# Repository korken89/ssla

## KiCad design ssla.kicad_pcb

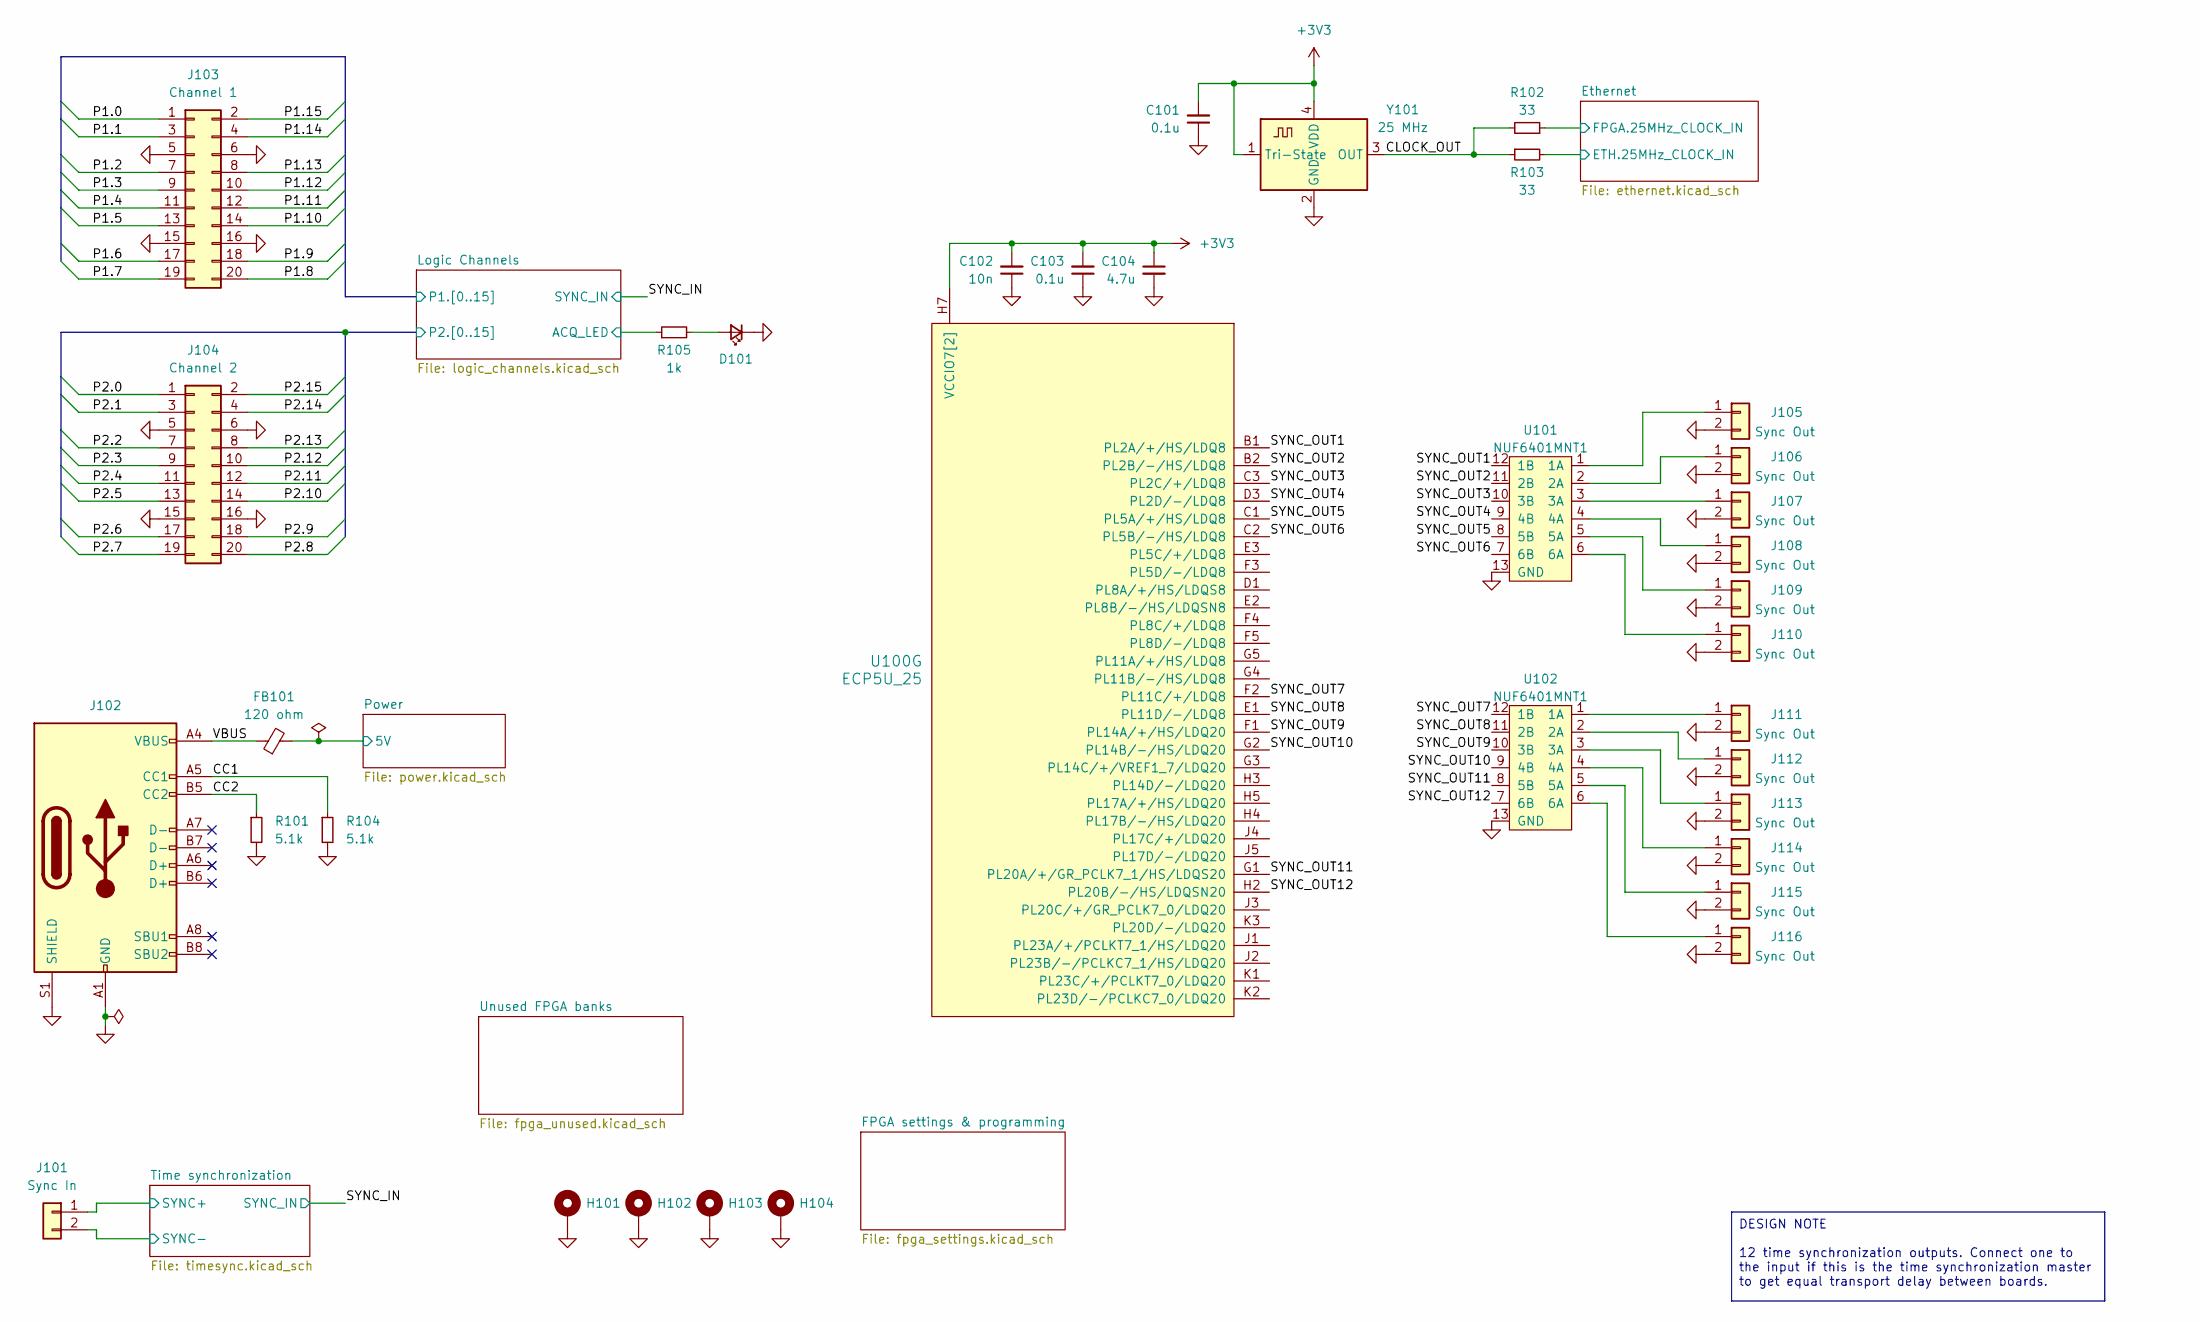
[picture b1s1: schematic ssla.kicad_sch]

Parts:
C101, C103: 0.1u; C_0402_1005Metric; LCSC C307331
C102: 10n; C_0402_1005Metric; LCSC C15195
C104: 4.7u; C_0402_1005Metric; LCSC C23733
D101: RED; LED_0603_1608Metric
FB101: 120 ohm; L_0402_1005Metric; LCSC C88970
H101, H102, H103, H104: MountingHole_Pad; MountingHole_2.2mm_M2_Pad_Via
J101: Sync In; JST_PH_B2B-PH-K_1x02_P2.00mm_Vertical; LCSC C158012
J102: USB_C_Receptacle_USB2.0_14P; USB_C_Receptacle_GCT_USB4105-xx-A_16P_TopMnt_Horizontal; LCSC C165948
J103: Channel 1; IDC-Header_2x10_P2.54mm_Vertical; LCSC C221051
J104: Channel 2; IDC-Header_2x10_P2.54mm_Vertical; LCSC C221051
J105, J106, J107, J108, J109, J110, J111, J112, J113, J114, J115, J116: Sync Out; JST_PH_B2B-PH-K_1x02_P2.00mm_Vertical; LCSC C158012
R101, R104: 5.1k; R_0402_1005Metric; LCSC C25905
R102, R103: 33; R_0402_1005Metric; LCSC C25105
R105: 1k; R_0402_1005Metric; LCSC C11702
U100: ECP5U_25; BGA-256_14.0x14.0mm_Layout16x16_P0.8mm_Ball0.45mm_Pad0.32mm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
U101, U102: NUF6401MNT1; DFN-12-1EP_1.35x3mm_P0.5mm; LCSC C233491
Y101: 25 MHz; Oscillator_SMD_SiT_PQFN-4Pin_2.0x1.6mm; LCSC C669080

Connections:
+3V3: C101.2, C102.2, C103.2, C104.1, U100.H6 (VCCIO7[2]), U100.H7 (VCCIO7[2]), Y101.1 (Tri-State), Y101.4 (VDD); also elsewhere on the board
/CC1: J102.A5 (CC1), R104.1
/CC2: J102.B5 (CC2), R101.1
/CLOCK_OUT: R102.2, R103.1, Y101.3 (OUT)
/Ethernet/ETH.25MHz_CLOCK_IN: R103.2; also elsewhere on the board
/Ethernet/FPGA.25MHz_CLOCK_IN: R102.1; also elsewhere on the board
/Logic Channels/ACQ_LED: R105.1; also elsewhere on the board
/Logic Channels/P1.0: J103.1; also elsewhere on the board
/Logic Channels/P1.1: J103.3; also elsewhere on the board
/Logic Channels/P1.2: J103.7; also elsewhere on the board
/Logic Channels/P1.3: J103.9; also elsewhere on the board
/Logic Channels/P1.4: J103.11; also elsewhere on the board
/Logic Channels/P1.5: J103.13; also elsewhere on the board
/Logic Channels/P1.6: J103.17; also elsewhere on the board
/Logic Channels/P1.7: J103.19; also elsewhere on the board
/Logic Channels/P1.8: J103.20; also elsewhere on the board
/Logic Channels/P1.9: J103.18; also elsewhere on the board
/Logic Channels/P1.10: J103.14; also elsewhere on the board
/Logic Channels/P1.11: J103.12; also elsewhere on the board
/Logic Channels/P1.12: J103.10; also elsewhere on the board
/Logic Channels/P1.13: J103.8; also elsewhere on the board
/Logic Channels/P1.14: J103.4; also elsewhere on the board
/Logic Channels/P1.15: J103.2; also elsewhere on the board
/Logic Channels/P2.0: J104.1; also elsewhere on the board
/Logic Channels/P2.1: J104.3; also elsewhere on the board
/Logic Channels/P2.2: J104.7; also elsewhere on the board
/Logic Channels/P2.3: J104.9; also elsewhere on the board
/Logic Channels/P2.4: J104.11; also elsewhere on the board
/Logic Channels/P2.5: J104.13; also elsewhere on the board
/Logic Channels/P2.6: J104.17; also elsewhere on the board
/Logic Channels/P2.7: J104.19; also elsewhere on the board
/Logic Channels/P2.8: J104.20; also elsewhere on the board
/Logic Channels/P2.9: J104.18; also elsewhere on the board
/Logic Channels/P2.10: J104.14; also elsewhere on the board
/Logic Channels/P2.11: J104.12; also elsewhere on the board
/Logic Channels/P2.12: J104.10; also elsewhere on the board
/Logic Channels/P2.13: J104.8; also elsewhere on the board
/Logic Channels/P2.14: J104.4; also elsewhere on the board
/Logic Channels/P2.15: J104.2; also elsewhere on the board
/Power/5V: FB101.2; also elsewhere on the board
/SYNC_OUT1: U100.B1 (PL2A/+/HS/LDQ8), U101.12 (1B)
/SYNC_OUT2: U100.B2 (PL2B/-/HS/LDQ8), U101.11 (2B)
/SYNC_OUT3: U100.C3 (PL2C/+/LDQ8), U101.10 (3B)
/SYNC_OUT4: U100.D3 (PL2D/-/LDQ8), U101.9 (4B)
/SYNC_OUT5: U100.C1 (PL5A/+/HS/LDQ8), U101.8 (5B)
/SYNC_OUT6: U100.C2 (PL5B/-/HS/LDQ8), U101.7 (6B)
/SYNC_OUT7: U100.F2 (PL11C/+/LDQ8), U102.12 (1B)
/SYNC_OUT8: U100.E1 (PL11D/-/LDQ8), U102.11 (2B)
/SYNC_OUT9: U100.F1 (PL14A/+/HS/LDQ20), U102.10 (3B)
/SYNC_OUT10: U100.G2 (PL14B/-/HS/LDQ20), U102.9 (4B)
/SYNC_OUT11: U100.G1 (PL20A/+/GR_PCLK7_1/HS/LDQS20), U102.8 (5B)
/SYNC_OUT12: U100.H2 (PL20B/-/HS/LDQSN20), U102.7 (6B)
/Time synchronization/SYNC+: J101.1; also elsewhere on the board
/Time synchronization/SYNC-: J101.2; also elsewhere on the board
/VBUS: FB101.1, J102.A4 (VBUS), J102.A9 (VBUS), J102.B4 (VBUS), J102.B9 (VBUS)
GND: C101.1, C102.1, C103.1, C104.2, D101.1 (K), H101.1, H102.1, H103.1, H104.1, J102.A1 (GND), J102.A12 (GND), J102.B1 (GND), J102.B12 (GND), J102.S1 (SHIELD), J103.5, J103.6, J103.15, J103.16, J104.5, J104.6, J104.15, J104.16, J105.2, J106.2, J107.2, J108.2, J109.2, J110.2, J111.2, J112.2, J113.2, J114.2, J115.2, J116.2, R101.2, R104.2, U101.13 (GND), U102.13 (GND), Y101.2 (GND); also elsewhere on the board
unnamed: D101.2 (A), R105.2
unnamed: J105.1, U101.1 (1A)
unnamed: J106.1, U101.2 (2A)
unnamed: J107.1, U101.3 (3A)
unnamed: J108.1, U101.4 (4A)
unnamed: J109.1, U101.5 (5A)
unnamed: J110.1, U101.6 (6A)
unnamed: J111.1, U102.1 (1A)
unnamed: J112.1, U102.2 (2A)
unnamed: J113.1, U102.3 (3A)
unnamed: J114.1, U102.4 (4A)
unnamed: J115.1, U102.5 (5A)
unnamed: J116.1, U102.6 (6A)

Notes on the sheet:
DESIGN NOTE 12 time synchronization outputs. Connect one to the input if this is the time synchronization master to get equal transport delay between boards.

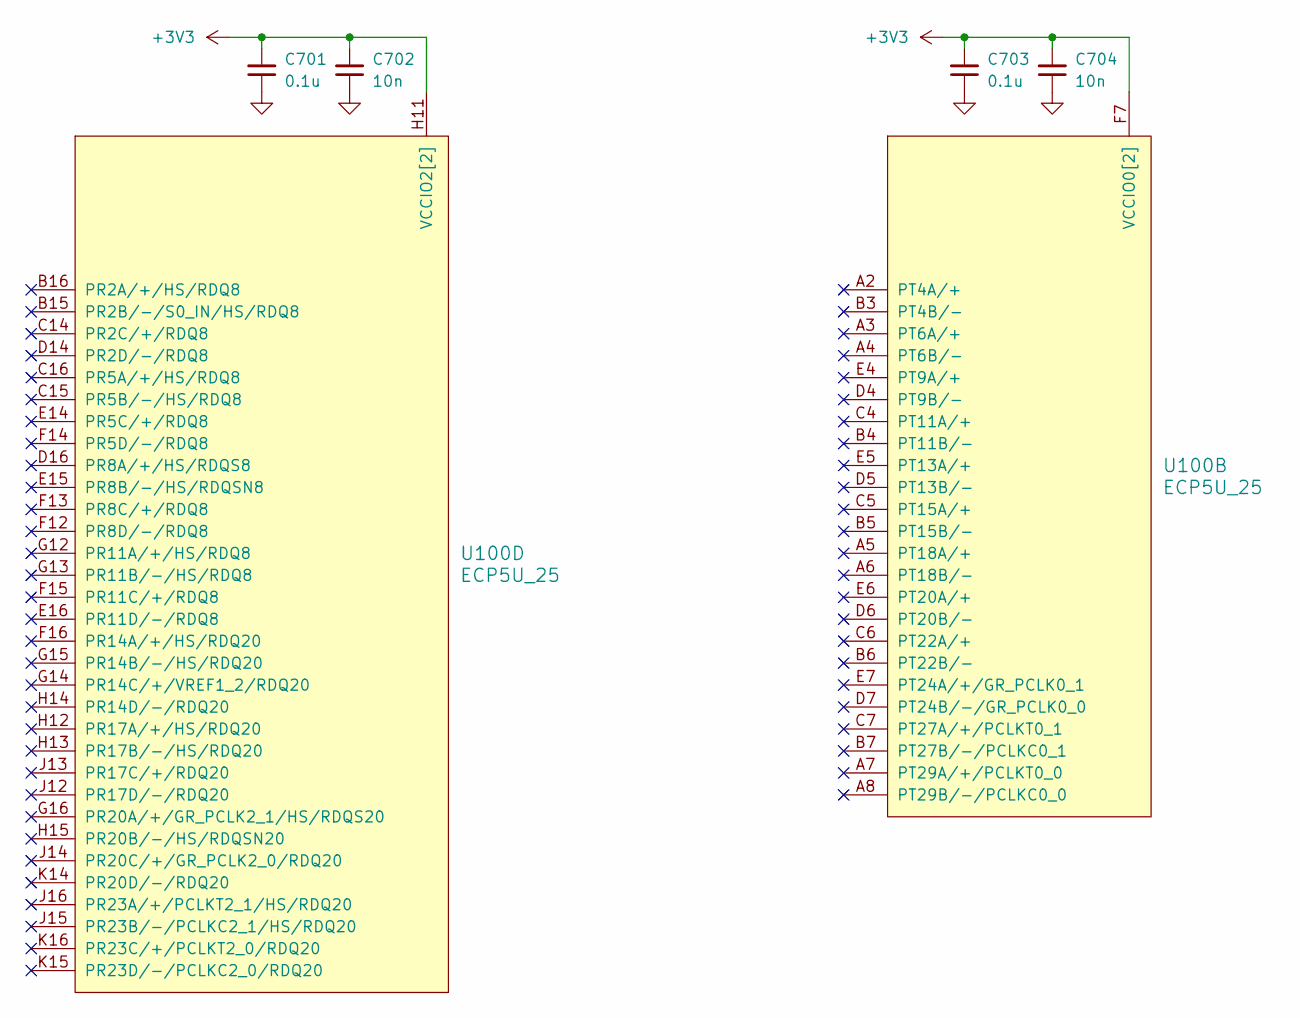
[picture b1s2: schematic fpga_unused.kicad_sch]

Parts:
C701, C703: 0.1u; C_0402_1005Metric; LCSC C307331
C702, C704: 10n; C_0402_1005Metric; LCSC C15195
U100: ECP5U_25; BGA-256_14.0x14.0mm_Layout16x16_P0.8mm_Ball0.45mm_Pad0.32mm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

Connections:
+3V3: C701.2, C702.2, C703.2, C704.2, U100.F6 (VCCIO0[2]), U100.F7 (VCCIO0[2]), U100.H11 (VCCIO2[2]), U100.J11 (VCCIO2[2]); also elsewhere on the board
GND: C701.1, C702.1, C703.1, C704.1; also elsewhere on the board

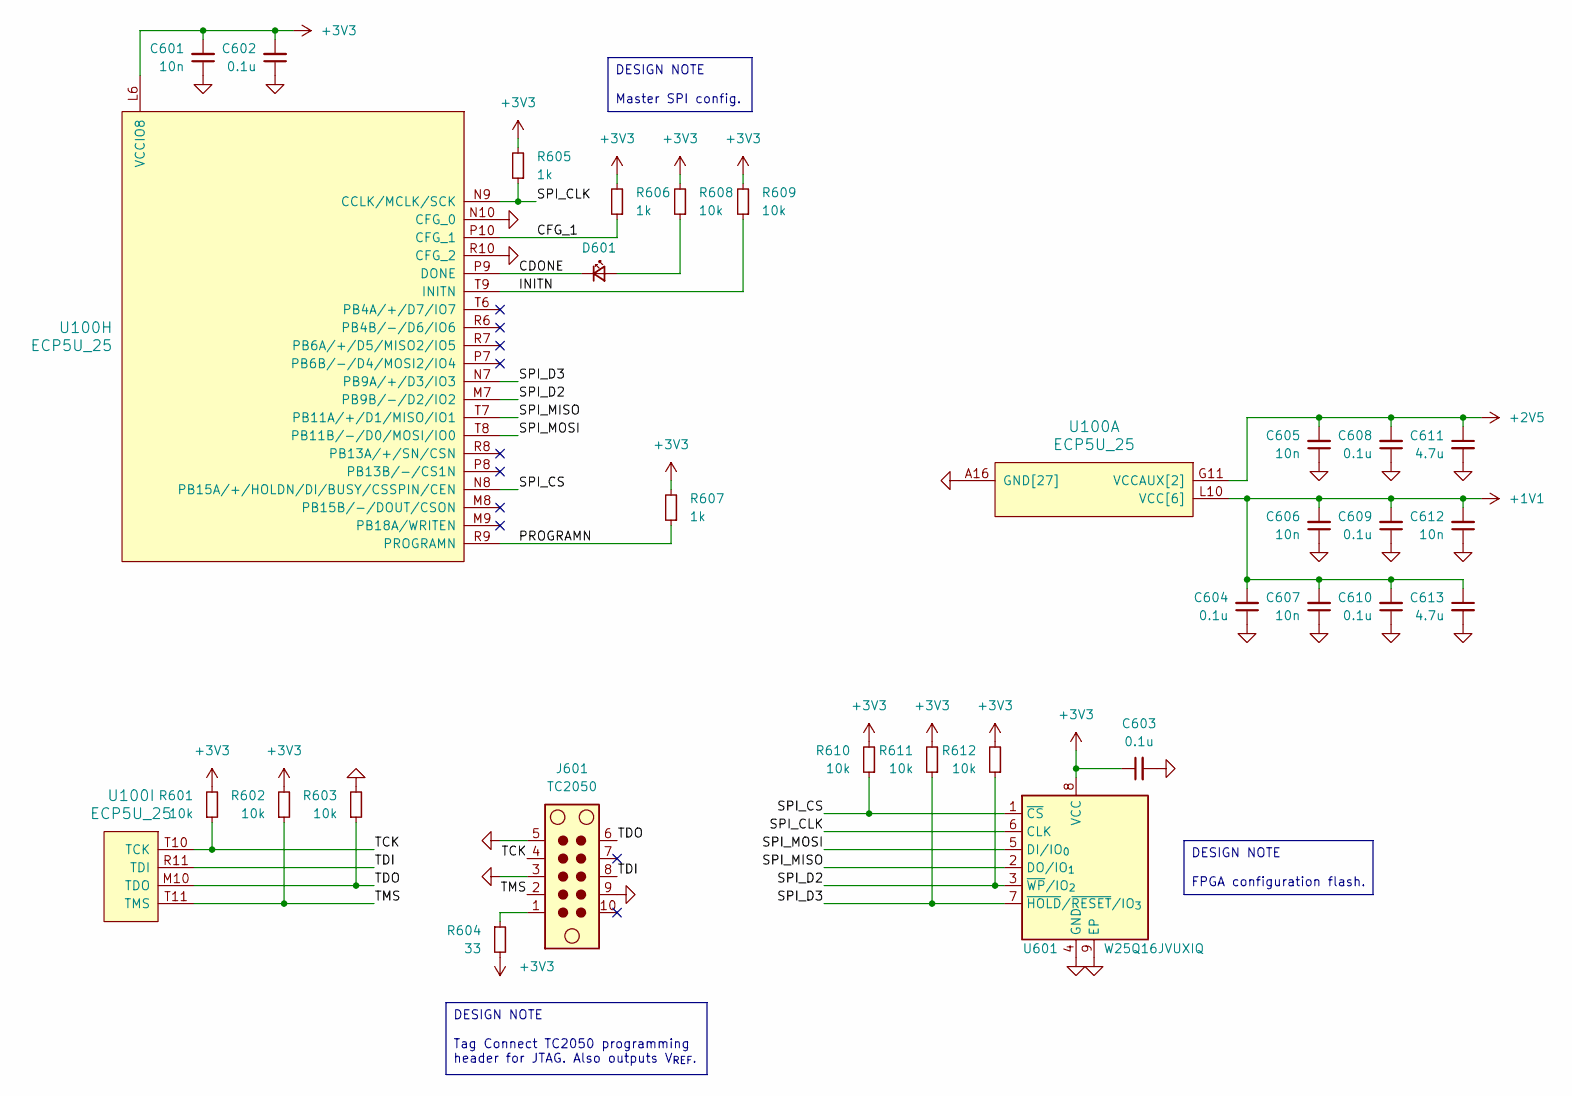
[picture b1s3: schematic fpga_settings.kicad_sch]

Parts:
C601, C605, C606, C607, C612: 10n; C_0402_1005Metric; LCSC C15195
C602, C603, C604, C608, C609, C610: 0.1u; C_0402_1005Metric; LCSC C307331
C611, C613: 4.7u; C_0402_1005Metric; LCSC C23733
D601: RED; LED_0603_1608Metric
J601: TC2050; Tag-Connect_TC2050-IDC-NL_2x05_P1.27mm_Vertical
R601, R602, R603, R608, R609, R610, R611, R612: 10k; R_0402_1005Metric; LCSC C25744
R604: 33; R_0402_1005Metric; LCSC C25105
R605, R606, R607: 1k; R_0402_1005Metric; LCSC C11702
U100: ECP5U_25; BGA-256_14.0x14.0mm_Layout16x16_P0.8mm_Ball0.45mm_Pad0.32mm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
U601: W25Q16JVUXIQ; Winbond_USON-8-1EP_3x2mm_P0.5mm_EP0.2x1.6mm; LCSC C2843335

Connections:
+1V1: C604.2, C606.2, C607.2, C609.2, C610.2, C612.2, C613.1, U100.G6 (VCC[6]), U100.G7 (VCC[6]), U100.G9 (VCC[6]), U100.L8 (VCC[6]), U100.L9 (VCC[6]), U100.L10 (VCC[6]); also elsewhere on the board
+2V5: C605.2, C608.2, C611.1, U100.G11 (VCCAUX[2]), U100.L7 (VCCAUX[2]); also elsewhere on the board
+3V3: C601.2, C602.2, C603.1, R601.2, R602.2, R604.2, R605.2, R606.2, R607.2, R608.2, R609.2, R610.2, R611.2, R612.2, U100.L6 (VCCIO8), U601.8 (VCC); also elsewhere on the board
/FPGA settings & programming/CDONE: D601.1 (K), U100.P9 (DONE)
/FPGA settings & programming/CFG_1: R606.1, U100.P10 (CFG_1)
/FPGA settings & programming/INITN: R609.1, U100.T9 (INITN)
/FPGA settings & programming/PROGRAMN: R607.1, U100.R9 (PROGRAMN)
/FPGA settings & programming/SPI_CLK: R605.1, U100.N9 (CCLK/MCLK/SCK), U601.6 (CLK)
/FPGA settings & programming/SPI_CS: R610.1, U100.N8 (PB15A/+/HOLDN/DI/BUSY/CSSPIN/CEN), U601.1 (~CS)
/FPGA settings & programming/SPI_D2: R612.1, U100.M7 (PB9B/-/D2/IO2), U601.3 (~WP/IO_{2})
/FPGA settings & programming/SPI_D3: R611.1, U100.N7 (PB9A/+/D3/IO3), U601.7 (~HOLD/~RESET/IO_{3})
/FPGA settings & programming/SPI_MISO: U100.T7 (PB11A/+/D1/MISO/IO1), U601.2 (DO/IO_{1})
/FPGA settings & programming/SPI_MOSI: U100.T8 (PB11B/-/D0/MOSI/IO0), U601.5 (DI/IO_{0})
/FPGA settings & programming/TCK: J601.4, R601.1, U100.T10 (TCK)
/FPGA settings & programming/TDI: J601.8, U100.R11 (TDI)
/FPGA settings & programming/TDO: J601.6, R603.1, U100.M10 (TDO)
/FPGA settings & programming/TMS: J601.2, R602.1, U100.T11 (TMS)
GND: C601.1, C602.1, C603.2, C604.1, C605.1, C606.1, C607.1, C608.1, C609.1, C610.1, C611.2, C612.1, C613.2, J601.3, J601.5, J601.9, R603.2, U100.A1 (GND[27]), U100.A16 (GND[27]), U100.D2 (GND[27]), U100.D15 (GND[27]), U100.F8 (GND[27]), U100.F9 (GND[27]), U100.G8 (GND[27]), U100.G10 (GND[27]), U100.H1 (GND[27]), U100.H8 (GND[27]), U100.H9 (GND[27]), U100.H10 (GND[27]), U100.H16 (GND[27]), U100.J8 (GND[27]), U100.J9 (GND[27]), U100.J10 (GND[27]), U100.K6 (GND[27]), U100.K7 (GND[27]), U100.K8 (GND[27]), U100.K9 (GND[27]), U100.K10 (GND[27]), U100.N2 (GND[27]), U100.N10 (CFG_0), U100.N15 (GND[27]), U100.R10 (CFG_2), U100.T1 (GND[27]), U100.T5 (GND[27]), U100.T12 (GND[27]), U100.T16 (GND[27]), U601.4 (GND), U601.9 (EP); also elsewhere on the board
unnamed: D601.2 (A), R608.1
unnamed: J601.1, R604.1

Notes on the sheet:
DESIGN NOTE FPGA configuration flash.
DESIGN NOTE Tag Connect TC2050 programming header for JTAG. Also outputs V_{REF}.
DESIGN NOTE Master SPI config.

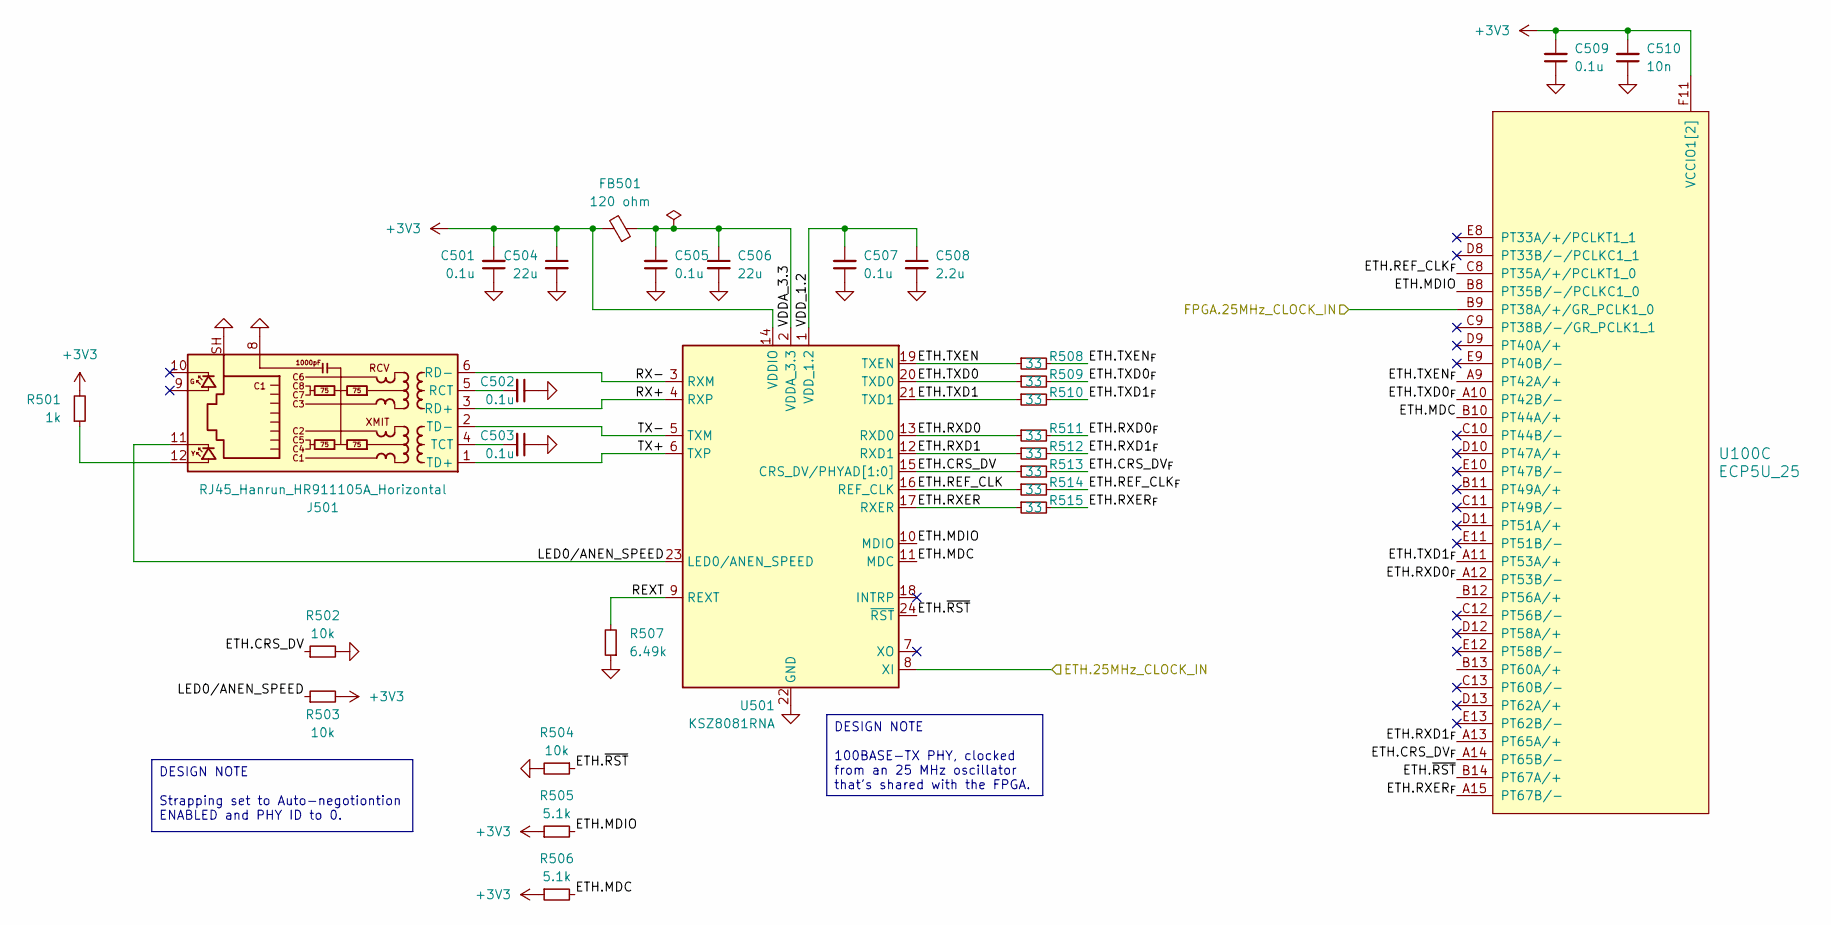
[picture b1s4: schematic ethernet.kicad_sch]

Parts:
C501, C502, C503, C505, C507, C509: 0.1u; C_0402_1005Metric; LCSC C307331
C504, C506: 22u; C_0603_1608Metric; LCSC C84419
C508: 2.2u; C_0402_1005Metric; LCSC C77002
C510: 10n; C_0402_1005Metric; LCSC C15195
FB501: 120 ohm; L_0402_1005Metric; LCSC C88970
J501: RJ45_Hanrun_HR911105A_Horizontal; LCSC C12074
R501: 1k; R_0402_1005Metric; LCSC C11702
R502, R503, R504: 10k; R_0402_1005Metric; LCSC C25744
R505, R506: 5.1k; R_0402_1005Metric; LCSC C25905
R507: 6.49k; R_0402_1005Metric; LCSC C25916
R508, R509, R510, R511, R512, R513, R514, R515: 33; R_0402_1005Metric; LCSC C25105
U100: ECP5U_25; BGA-256_14.0x14.0mm_Layout16x16_P0.8mm_Ball0.45mm_Pad0.32mm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
U501: KSZ8081RNA; QFN-24-1EP_4x4mm_P0.5mm_EP2.6x2.6mm; LCSC C100017

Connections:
+3V3: C501.2, C504.1, C509.2, C510.2, FB501.2, R501.2, R503.2, R505.1, R506.1, U100.F10 (VCCIO1[2]), U100.F11 (VCCIO1[2]), U501.14 (VDDIO); also elsewhere on the board
/Ethernet/ETH.25MHz_CLOCK_IN: U501.8 (XI); also elsewhere on the board
/Ethernet/ETH.CRS_DV: R502.1, R513.1, U501.15 (CRS_DV/PHYAD[1:0])
/Ethernet/ETH.CRS_DV_{F}: R513.2, U100.A14 (PT65B/-)
/Ethernet/ETH.MDC: R506.2, U100.B10 (PT44A/+), U501.11 (MDC)
/Ethernet/ETH.MDIO: R505.2, U100.B8 (PT35B/-/PCLKC1_0), U501.10 (MDIO)
/Ethernet/ETH.REF_CLK: R514.1, U501.16 (REF_CLK)
/Ethernet/ETH.REF_CLK_{F}: R514.2, U100.C8 (PT35A/+/PCLKT1_0)
/Ethernet/ETH.RXD0: R511.1, U501.13 (RXD0)
/Ethernet/ETH.RXD0_{F}: R511.2, U100.A12 (PT53B/-)
/Ethernet/ETH.RXD1: R512.1, U501.12 (RXD1)
/Ethernet/ETH.RXD1_{F}: R512.2, U100.A13 (PT65A/+)
/Ethernet/ETH.RXER: R515.1, U501.17 (RXER)
/Ethernet/ETH.RXER_{F}: R515.2, U100.A15 (PT67B/-)
/Ethernet/ETH.TXD0: R509.1, U501.20 (TXD0)
/Ethernet/ETH.TXD0_{F}: R509.2, U100.A10 (PT42B/-)
/Ethernet/ETH.TXD1: R510.1, U501.21 (TXD1)
/Ethernet/ETH.TXD1_{F}: R510.2, U100.A11 (PT53A/+)
/Ethernet/ETH.TXEN: R508.1, U501.19 (TXEN)
/Ethernet/ETH.TXEN_{F}: R508.2, U100.A9 (PT42A/+)
/Ethernet/ETH.~RST: R504.1, U100.B14 (PT67A/+), U501.24 (~RST)
/Ethernet/FPGA.25MHz_CLOCK_IN: U100.B9 (PT38A/+/GR_PCLK1_0); also elsewhere on the board
/Ethernet/LED0/ANEN_SPEED: J501.11, R503.1, U501.23 (LED0/ANEN_SPEED)
/Ethernet/REXT: R507.2, U501.9 (REXT)
/Ethernet/RX+: J501.3 (RD+), U501.4 (RXP)
/Ethernet/RX-: J501.6 (RD-), U501.3 (RXM)
/Ethernet/TX+: J501.1 (TD+), U501.6 (TXP)
/Ethernet/TX-: J501.2 (TD-), U501.5 (TXM)
/Ethernet/VDDA_3.3: C505.2, C506.1, FB501.1, U501.2 (VDDA_3.3)
/Ethernet/VDD_1.2: C507.2, C508.1, U501.1 (VDD_1.2)
GND: C501.1, C502.1, C503.1, C504.2, C505.1, C506.2, C507.1, C508.2, C509.1, C510.1, J501.8, J501.SH, R502.2, R504.2, R507.1, U501.22 (GND), U501.25 (GND); also elsewhere on the board
unnamed: J501.12, R501.1
unnamed: C502.2, J501.5 (RCT)
unnamed: C503.2, J501.4 (TCT)

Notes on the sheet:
DESIGN NOTE 100BASE-TX PHY, clocked from an 25 MHz oscillator that's shared with the FPGA.
DESIGN NOTE Strapping set to Auto-negotiontion ENABLED and PHY ID to 0.

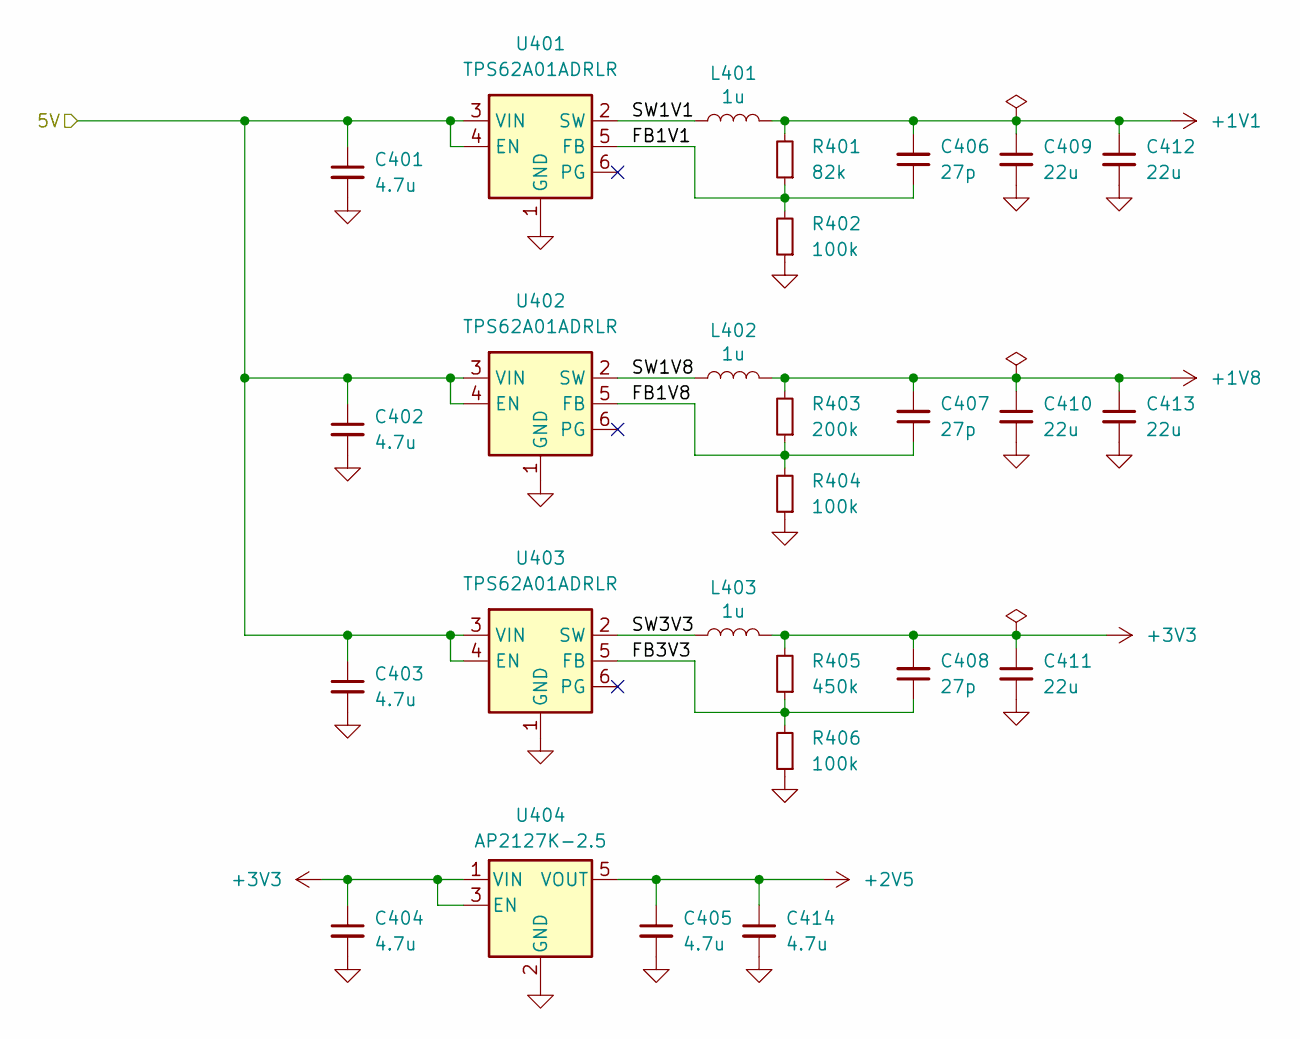
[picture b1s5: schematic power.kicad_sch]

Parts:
C401, C402, C403, C404, C405, C414: 4.7u; C_0402_1005Metric; LCSC C23733
C406, C407, C408: 27p; C_0402_1005Metric; LCSC C126504
C409, C410, C411, C412, C413: 22u; C_0603_1608Metric; LCSC C84419
L401, L402, L403: 1u; L_0805_2012Metric; LCSC C20770353
R401: 82k; R_0402_1005Metric; LCSC C4142
R402, R404, R406: 100k; R_0402_1005Metric; LCSC C25741
R403: 200k; R_0402_1005Metric; LCSC C25764
R405: 450k; R_0402_1005Metric; LCSC C5159688
U401, U402, U403: TPS62A01ADRLR; SOT-563; LCSC C5181455
U404: AP2127K-2.5; SOT-23-5; LCSC C460326

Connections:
+1V1: C406.2, C409.1, C412.1, L401.2, R401.2; also elsewhere on the board
+1V8: C407.2, C410.1, C413.1, L402.2, R403.2; also elsewhere on the board
+2V5: C405.1, C414.1, U404.5 (VOUT); also elsewhere on the board
+3V3: C404.1, C408.2, C411.1, L403.2, R405.2, U404.1 (VIN), U404.3 (EN); also elsewhere on the board
/Power/5V: C401.1, C402.1, C403.1, U401.3 (VIN), U401.4 (EN), U402.3 (VIN), U402.4 (EN), U403.3 (VIN), U403.4 (EN); also elsewhere on the board
/Power/FB1V1: C406.1, R401.1, R402.2, U401.5 (FB)
/Power/FB1V8: C407.1, R403.1, R404.2, U402.5 (FB)
/Power/FB3V3: C408.1, R405.1, R406.2, U403.5 (FB)
/Power/SW1V1: L401.1, U401.2 (SW)
/Power/SW1V8: L402.1, U402.2 (SW)
/Power/SW3V3: L403.1, U403.2 (SW)
GND: C401.2, C402.2, C403.2, C404.2, C405.2, C409.2, C410.2, C411.2, C412.2, C413.2, C414.2, R402.1, R404.1, R406.1, U401.1 (GND), U402.1 (GND), U403.1 (GND), U404.2 (GND); also elsewhere on the board

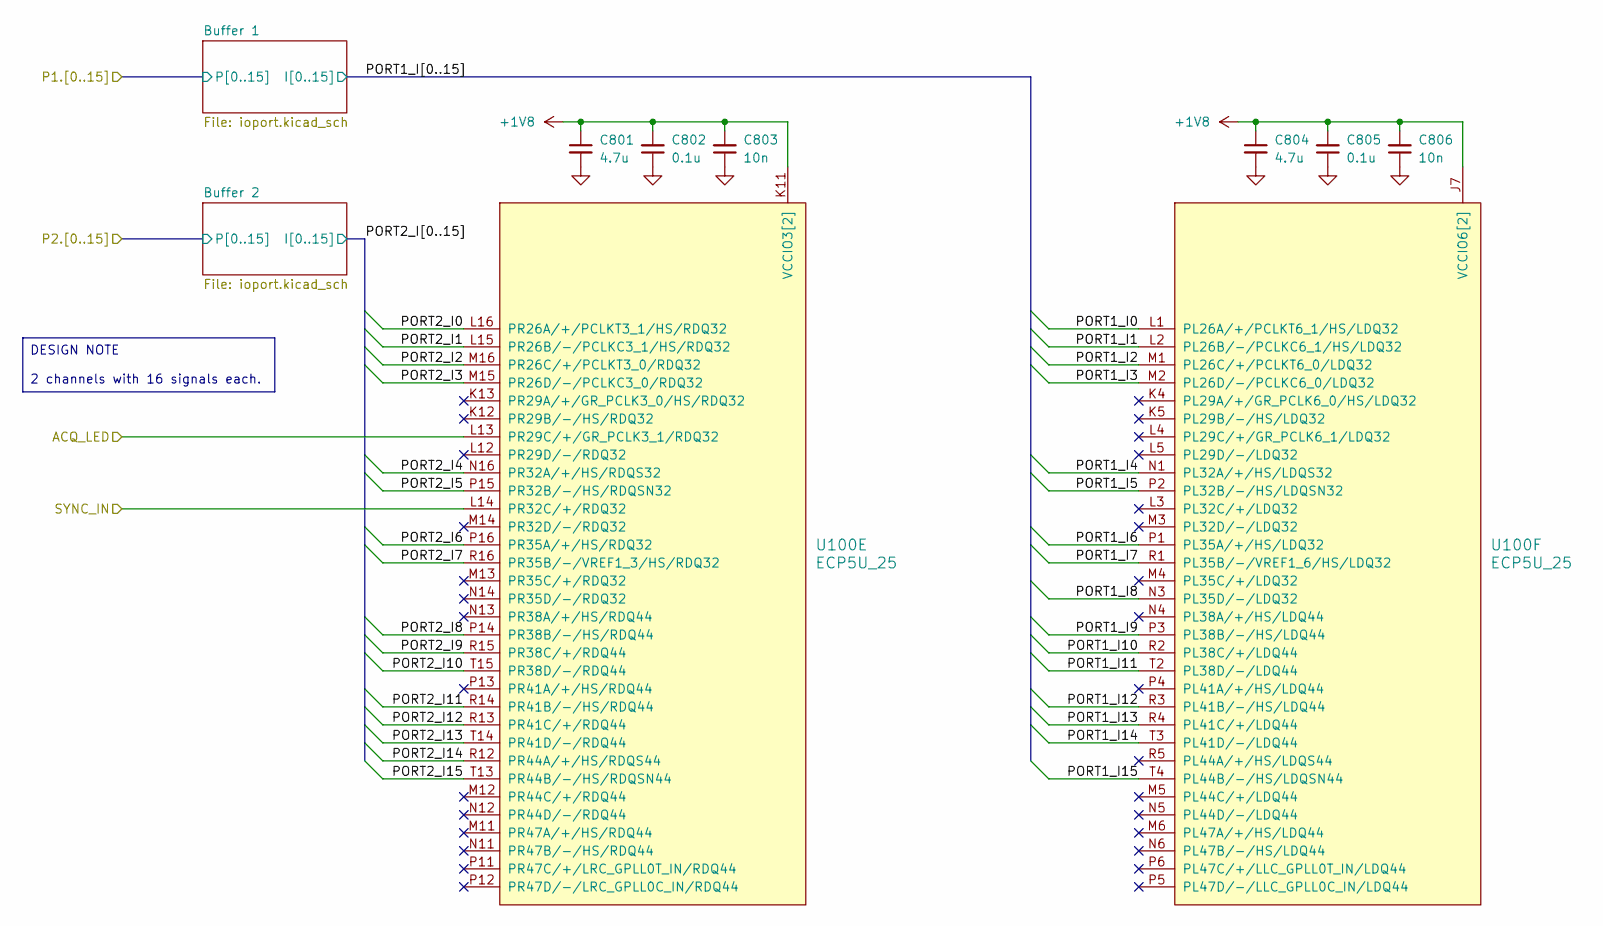
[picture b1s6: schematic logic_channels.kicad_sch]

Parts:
C801, C804: 4.7u; C_0402_1005Metric; LCSC C23733
C802, C805: 0.1u; C_0402_1005Metric; LCSC C307331
C803, C806: 10n; C_0402_1005Metric; LCSC C15195
U100: ECP5U_25; BGA-256_14.0x14.0mm_Layout16x16_P0.8mm_Ball0.45mm_Pad0.32mm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

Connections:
+1V8: C801.1, C802.2, C803.2, C804.1, C805.2, C806.2, U100.J6 (VCCIO6[2]), U100.J7 (VCCIO6[2]), U100.K11 (VCCIO3[2]), U100.L11 (VCCIO3[2]); also elsewhere on the board
/Logic Channels/ACQ_LED: U100.L13 (PR29C/+/GR_PCLK3_1/RDQ32); also elsewhere on the board
/Logic Channels/PORT1_I0: U100.L1 (PL26A/+/PCLKT6_1/HS/LDQ32); also elsewhere on the board
/Logic Channels/PORT1_I1: U100.L2 (PL26B/-/PCLKC6_1/HS/LDQ32); also elsewhere on the board
/Logic Channels/PORT1_I2: U100.M1 (PL26C/+/PCLKT6_0/LDQ32); also elsewhere on the board
/Logic Channels/PORT1_I3: U100.M2 (PL26D/-/PCLKC6_0/LDQ32); also elsewhere on the board
/Logic Channels/PORT1_I4: U100.N1 (PL32A/+/HS/LDQS32); also elsewhere on the board
/Logic Channels/PORT1_I5: U100.P2 (PL32B/-/HS/LDQSN32); also elsewhere on the board
/Logic Channels/PORT1_I6: U100.P1 (PL35A/+/HS/LDQ32); also elsewhere on the board
/Logic Channels/PORT1_I7: U100.R1 (PL35B/-/VREF1_6/HS/LDQ32); also elsewhere on the board
/Logic Channels/PORT1_I8: U100.N3 (PL35D/-/LDQ32); also elsewhere on the board
/Logic Channels/PORT1_I9: U100.P3 (PL38B/-/HS/LDQ44); also elsewhere on the board
/Logic Channels/PORT1_I10: U100.R2 (PL38C/+/LDQ44); also elsewhere on the board
/Logic Channels/PORT1_I11: U100.T2 (PL38D/-/LDQ44); also elsewhere on the board
/Logic Channels/PORT1_I12: U100.R3 (PL41B/-/HS/LDQ44); also elsewhere on the board
/Logic Channels/PORT1_I13: U100.R4 (PL41C/+/LDQ44); also elsewhere on the board
/Logic Channels/PORT1_I14: U100.T3 (PL41D/-/LDQ44); also elsewhere on the board
/Logic Channels/PORT1_I15: U100.T4 (PL44B/-/HS/LDQSN44); also elsewhere on the board
/Logic Channels/PORT2_I0: U100.L16 (PR26A/+/PCLKT3_1/HS/RDQ32); also elsewhere on the board
/Logic Channels/PORT2_I1: U100.L15 (PR26B/-/PCLKC3_1/HS/RDQ32); also elsewhere on the board
/Logic Channels/PORT2_I2: U100.M16 (PR26C/+/PCLKT3_0/RDQ32); also elsewhere on the board
/Logic Channels/PORT2_I3: U100.M15 (PR26D/-/PCLKC3_0/RDQ32); also elsewhere on the board
/Logic Channels/PORT2_I4: U100.N16 (PR32A/+/HS/RDQS32); also elsewhere on the board
/Logic Channels/PORT2_I5: U100.P15 (PR32B/-/HS/RDQSN32); also elsewhere on the board
/Logic Channels/PORT2_I6: U100.P16 (PR35A/+/HS/RDQ32); also elsewhere on the board
/Logic Channels/PORT2_I7: U100.R16 (PR35B/-/VREF1_3/HS/RDQ32); also elsewhere on the board
/Logic Channels/PORT2_I8: U100.P14 (PR38B/-/HS/RDQ44); also elsewhere on the board
/Logic Channels/PORT2_I9: U100.R15 (PR38C/+/RDQ44); also elsewhere on the board
/Logic Channels/PORT2_I10: U100.T15 (PR38D/-/RDQ44); also elsewhere on the board
/Logic Channels/PORT2_I11: U100.R14 (PR41B/-/HS/RDQ44); also elsewhere on the board
/Logic Channels/PORT2_I12: U100.R13 (PR41C/+/RDQ44); also elsewhere on the board
/Logic Channels/PORT2_I13: U100.T14 (PR41D/-/RDQ44); also elsewhere on the board
/Logic Channels/PORT2_I14: U100.R12 (PR44A/+/HS/RDQS44); also elsewhere on the board
/Logic Channels/PORT2_I15: U100.T13 (PR44B/-/HS/RDQSN44); also elsewhere on the board
/SYNC_IN: U100.L14 (PR32C/+/RDQ32); also elsewhere on the board
GND: C801.2, C802.1, C803.1, C804.2, C805.1, C806.1; also elsewhere on the board

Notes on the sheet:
DESIGN NOTE 2 channels with 16 signals each.

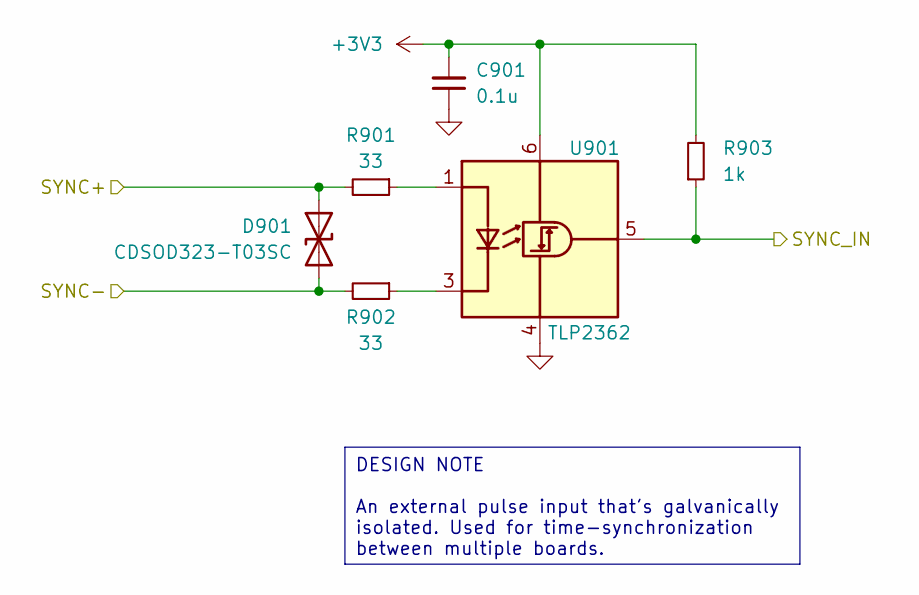
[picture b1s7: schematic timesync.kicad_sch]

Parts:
C901: 0.1u; C_0402_1005Metric; LCSC C307331
D901: CDSOD323-T03SC; D_SOD-323; LCSC C840638
R901, R902: 33; R_0402_1005Metric; LCSC C25105
R903: 1k; R_0402_1005Metric; LCSC C11702
U901: TLP2362; SO-5-6_4.55x3.7mm_P1.27mm; LCSC C37658

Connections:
+3V3: C901.2, R903.2, U901.6 (VDD); also elsewhere on the board
/SYNC_IN: R903.1, U901.5 (VO); also elsewhere on the board
/Time synchronization/SYNC+: D901.1 (A1), R901.2; also elsewhere on the board
/Time synchronization/SYNC-: D901.2 (A2), R902.2; also elsewhere on the board
GND: C901.1, U901.4 (GND); also elsewhere on the board
unnamed: R901.1, U901.1 (A)
unnamed: R902.1, U901.3 (K)

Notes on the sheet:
DESIGN NOTE An external pulse input that's galvanically isolated. Used for time-synchronization between multiple boards.
